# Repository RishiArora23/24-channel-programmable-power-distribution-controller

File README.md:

# 24-Channel Programmable Power Distribution Controller

An ESP32-based programmable firing controller for sequenced 24-channel power distribution. The system combines embedded firmware, a KiCad-designed PCB, and a PyQt5 desktop application to enable fully programmable, remotely triggered output sequences — with hardware safety interlocks and a real-time TFT display.

> ⚠️ **Safety Notice:** This system switches high-current loads via power MOSFETs. Always follow applicable electrical safety guidelines. Never connect live loads during programming or testing.

---

## How It Works

Each of the 24 output channels is driven by an **IRLZ44N N-Channel MOSFET** (55 V, 47 A) switched via a **3× cascaded shift register** chain. The ESP32 clocks channel states into the shift registers over SPI, allowing all 24 outputs to be independently toggled in any order or pattern. A 12 V rail MOSFET acts as a master power switch, controlled by software arm/disarm commands.

The desktop app (`main.py`) communicates with the ESP32 over **Wi-Fi (TCP port 8080)** or via **UDP auto-discovery** (port 4210). Sequences are authored graphically in the app, serialized to JSON, and uploaded to the ESP32 at runtime — no re-flashing required.

---

## System Architecture

```
[ PyQt5 Desktop App ] ──WiFi TCP/UDP──► [ ESP32 Firmware ]
         │                                      │
   Sequence Editor                    Shift Registers (×3)
   Group/Pattern UI                         │
   Arm / Fire Controls              [ 24× IRLZ44N MOSFETs ]
                                            │
                                    [ Output Terminals J1–J24 ]
```

---

## Hardware

**Key components (from KiCad schematic):**
- **MCU:** ESP32 (Arduino framework)
- **Output switches:** 24× IRLZ44N MOSFETs in TO-220 package
- **Channel indicators:** 24× LEDs with 220 Ω series resistors
- **Gate drive:** 10 kΩ pull-down resistors per MOSFET gate
- **Shift registers:** 3× 8-bit shift registers (SRCLK → pin 23, RCLK → pin 21, SER → pin 22, OE → pin 19, SRCLR → pin 18)
- **Rail safety:** MOSFET switch on pin 27, analog voltage sense on pin 34
- **Display:** ILI9341 TFT (HSPI: MOSI 13, CLK 14, MISO 12, CS 5, DC 4, RST 17)
- **Output connectors:** 24× 2-pin 5.08 mm terminal blocks (J1–J24)

**Project files:**

| File | Description |
|------|-------------|
| `*.kicad_sch` | Schematic (channel sub-sheets × 24 + top sheet) |
| `*.kicad_pcb` | PCB layout |
| `*.kicad_pro` | KiCad project file |

---

## Firmware (`*.ino`)

Written in Arduino C++ for ESP32. Key responsibilities:

- **WiFiManager** captive portal for first-time Wi-Fi setup (AP: `Pyro-Setup-AP`)
- TCP server on port **8080** for desktop app communication
- UDP listener on port **4210** for auto-discovery
- Shift register management: channels fire for **1000 ms** then auto-clear
- JSON sequence parser (`ArduinoJson`) supporting up to **20 groups × 24 steps**
- Built-in web UI accessible from any browser on the network (manual fire, arm/disarm, sequence status)
- Real-time TFT UI with state machine: `IDLE → ARMED → COUNTDOWN → EXECUTING → FINISHED`

**ESP32 Pin Summary:**

| Function | Pin |
|----------|-----|
| Rail MOSFET (arm) | 27 |
| Rail voltage sense | 34 |
| Shift reg SRCLK | 23 |
| Shift reg RCLK | 21 |
| Shift reg SER | 22 |
| Shift reg OE | 19 |
| Shift reg SRCLR | 18 |
| TFT MOSI/CLK/MISO/CS/DC/RST | 13/14/12/5/4/17 |

---

## Desktop App (`main.py`)

PyQt5 GUI application. Requires Python 3 and the following packages:

```bash
pip install PyQt5 pyserial
```

**Features:**
- Initialize a sequence with N cues (up to 24)
- Build named **groups** with patterns: Right Wave, Left Wave, Alternate, Center Burst, Inwards, All Fire
- Set inter-step gap (ms) per group
- Upload sequence as JSON to ESP32 over Wi-Fi
- Arm/disarm rail, monitor live rail voltage safety status
- Countdown display and per-channel LED flash feedback
- Undo/redo, save/load sequences as JSON files (`Ctrl+S` / `Ctrl+O`)
- **UDP Auto-Discovery** — finds the ESP32 on the local network automatically

**To run:**
```bash
python main.py
```

On first launch, connect the ESP32 to Wi-Fi via the `Pyro-Setup-AP` captive portal, then use **Auto Connect** in the app to discover it.

---

## Repository Structure

```
├── *.ino               # ESP32 Arduino firmware
├── main.py             # PyQt5 desktop control application
├── *.kicad_sch         # KiCad schematics (top + 24 channel sub-sheets)
├── *.kicad_pcb         # PCB layout
└── *.kicad_pro         # KiCad project
```

---

## License

This project is licensed under the [MIT License](LICENSE).

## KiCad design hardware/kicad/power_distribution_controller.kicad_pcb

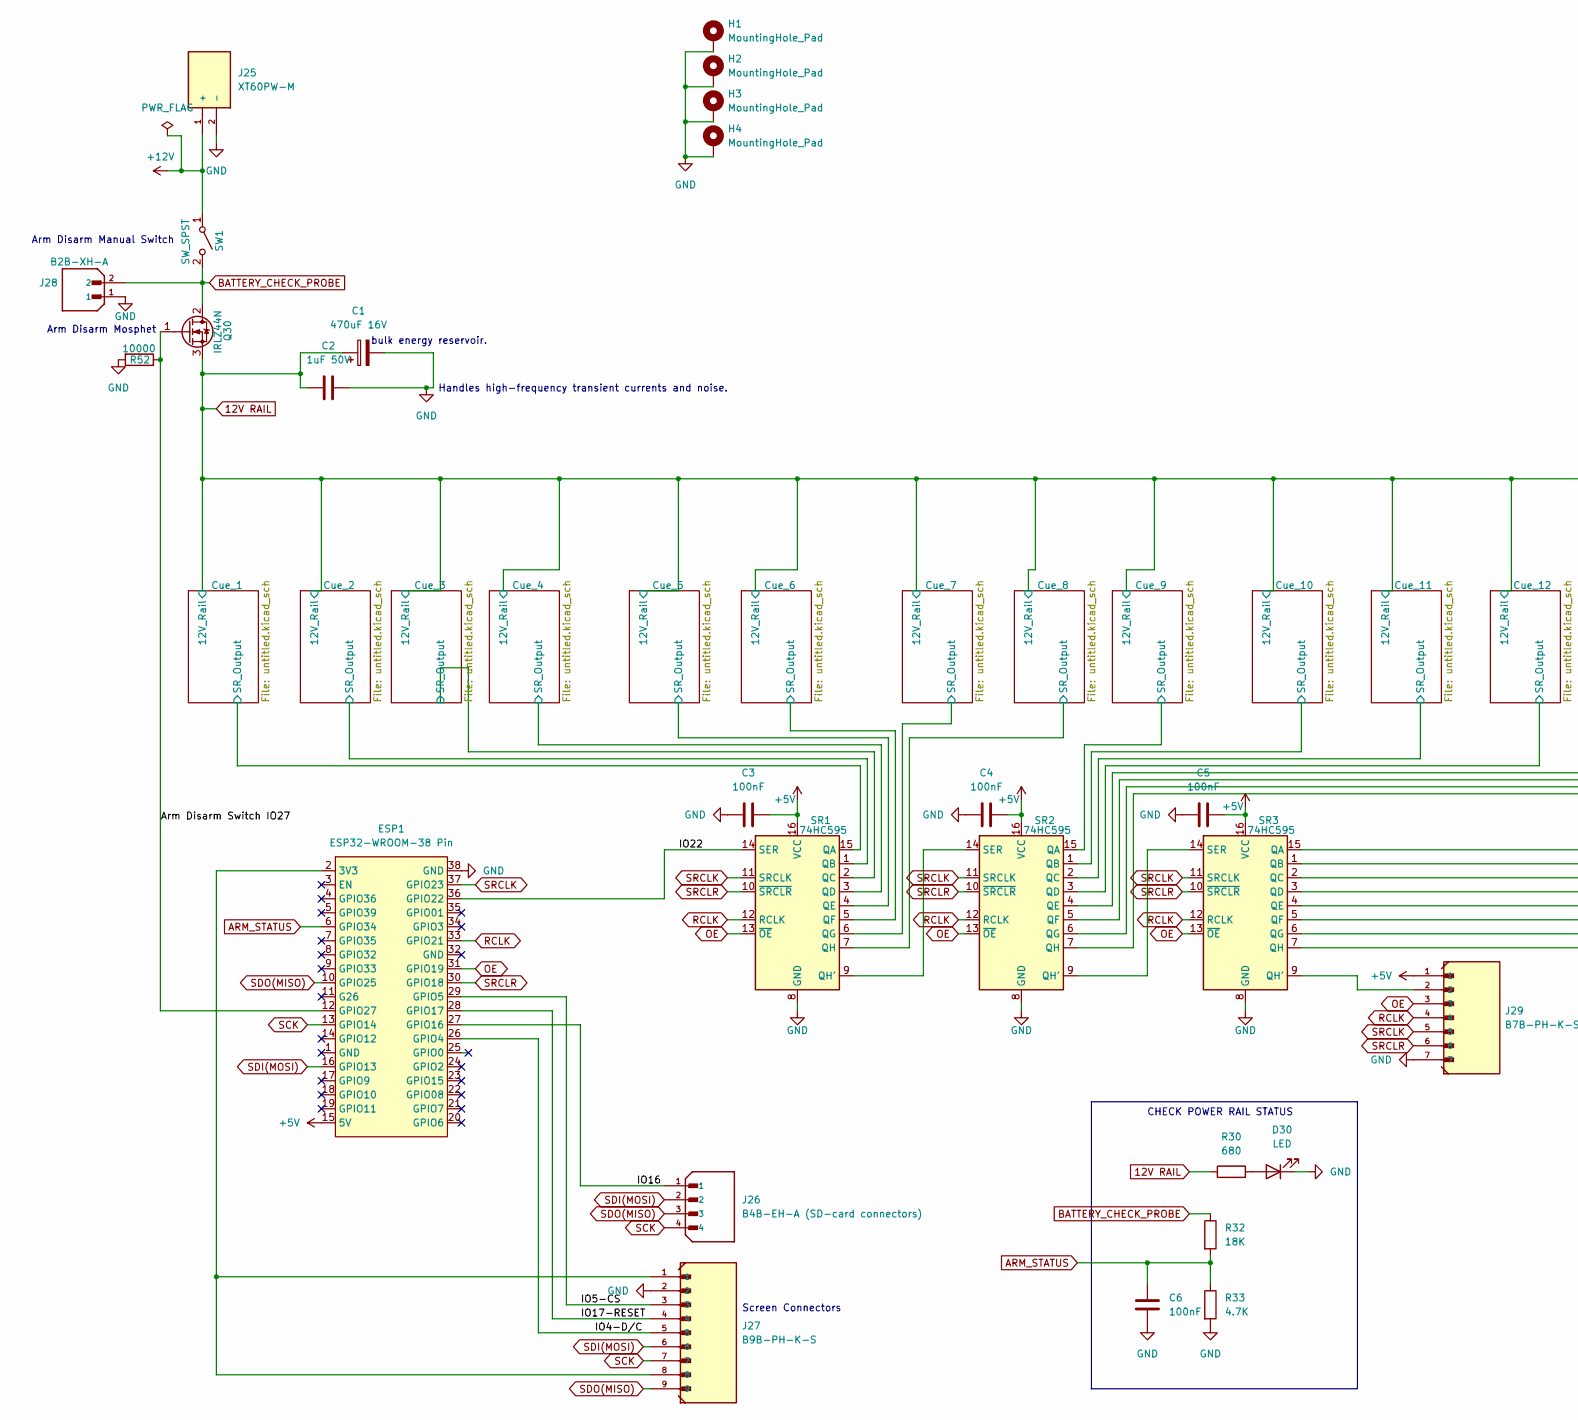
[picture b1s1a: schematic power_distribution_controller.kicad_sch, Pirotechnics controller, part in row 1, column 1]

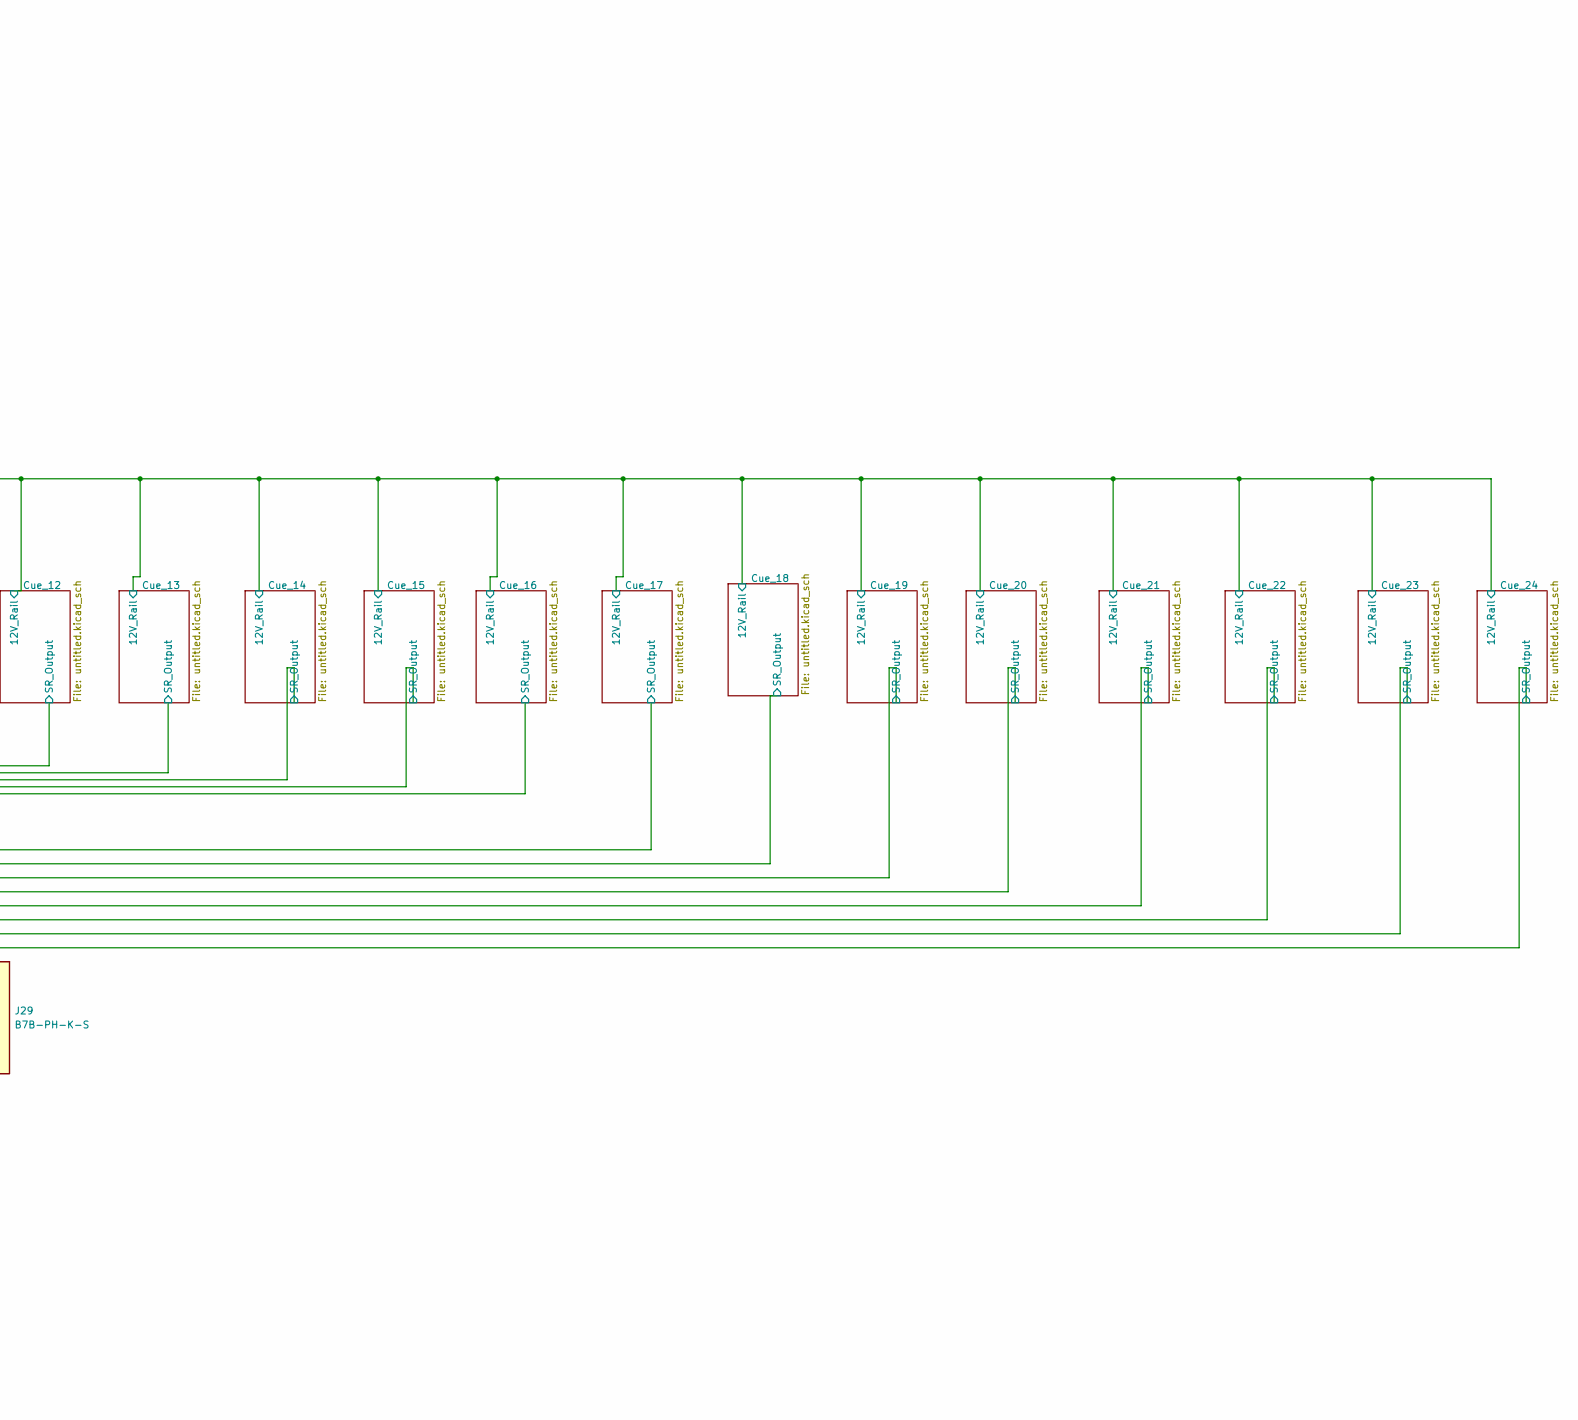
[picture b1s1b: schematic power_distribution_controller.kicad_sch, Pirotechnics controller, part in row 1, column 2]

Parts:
C1: 470uF 16V; CP_Radial_D10.0mm_P5.00mm
C2: 1uF 50V; CP_Radial_D5.0mm_P2.50mm
C3, C4, C5, C6: 100nF; C_0805_2012Metric_Pad1.18x1.45mm_HandSolder
D30: LED; LED_D5.0mm
ESP1: ESP32-WROOM-38 Pin; ESP32_38Pin_THT
H1, H2, H3, H4: MountingHole_Pad; MountingHole_3.2mm_M3_Pad
J25: XT60PW-M; AMASS_XT60PW-M; PARTREV V1.2
J26: B4B-EH-A (SD-card connectors); JST_PH_B4B-PH-K_1x04_P2.00mm_Vertical
J27: B9B-PH-K-S; JST_EH_B9B-EH-A_1x09_P2.50mm_Vertical
J28: B2B-XH-A; JST_B2B-XH-A; PARTREV N/A
J29: B7B-PH-K-S; JST_B7B-PH-K-S
Q30: IRLZ44N; TO-220-3_Vertical
R30: 680; R_0805_2012Metric_Pad1.20x1.40mm_HandSolder
R32: 18K; R_0805_2012Metric_Pad1.20x1.40mm_HandSolder
R33: 4.7K; R_0805_2012Metric_Pad1.20x1.40mm_HandSolder
R52: 10000; R_0805_2012Metric_Pad1.20x1.40mm_HandSolder
SR1, SR2, SR3: 74HC595; DIP-16_W7.62mm
SW1: SW_SPST; TerminalBlock_bornier-2_P5.08mm

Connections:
12V RAIL: C1.1, C2.1, Q30.3 (S), R30.1; also elsewhere on the board
+5V: C3.1, C4.1, C5.1, ESP1.15 (5V), J29.1, SR1.16 (VCC), SR2.16 (VCC), SR3.16 (VCC)
+12V: J25.1 (+), SW1.1 (A)
/Arm Disarm Switch IO27: ESP1.12 (GPIO27), Q30.1 (G), R52.1
/Cue_1/SR_Output: SR1.15 (QA); also elsewhere on the board
/Cue_2/SR_Output: SR1.1 (QB); also elsewhere on the board
/Cue_3/SR_Output: SR1.2 (QC); also elsewhere on the board
/Cue_4/SR_Output: SR1.3 (QD); also elsewhere on the board
/Cue_5/SR_Output: SR1.4 (QE); also elsewhere on the board
/Cue_6/SR_Output: SR1.5 (QF); also elsewhere on the board
/Cue_7/SR_Output: SR1.6 (QG); also elsewhere on the board
/Cue_8/SR_Output: SR1.7 (QH); also elsewhere on the board
/Cue_9/SR_Output: SR2.15 (QA); also elsewhere on the board
/Cue_10/SR_Output: SR2.1 (QB); also elsewhere on the board
/Cue_11/SR_Output: SR2.2 (QC); also elsewhere on the board
/Cue_12/SR_Output: SR2.3 (QD); also elsewhere on the board
/Cue_13/SR_Output: SR2.4 (QE); also elsewhere on the board
/Cue_14/SR_Output: SR2.5 (QF); also elsewhere on the board
/Cue_15/SR_Output: SR2.6 (QG); also elsewhere on the board
/Cue_16/SR_Output: SR2.7 (QH); also elsewhere on the board
/Cue_17/SR_Output: SR3.15 (QA); also elsewhere on the board
/Cue_18/SR_Output: SR3.1 (QB); also elsewhere on the board
/Cue_19/SR_Output: SR3.2 (QC); also elsewhere on the board
/Cue_20/SR_Output: SR3.3 (QD); also elsewhere on the board
/Cue_21/SR_Output: SR3.4 (QE); also elsewhere on the board
/Cue_22/SR_Output: SR3.5 (QF); also elsewhere on the board
/Cue_23/SR_Output: SR3.6 (QG); also elsewhere on the board
/Cue_24/SR_Output: SR3.7 (QH); also elsewhere on the board
/IO4-D/C: ESP1.26 (GPIO4), J27.5
/IO5-CS: ESP1.29 (GPIO5), J27.3
/IO16: ESP1.27 (GPIO16), J26.1
/IO17-RESET: ESP1.28 (GPIO17), J27.4
/IO22: ESP1.36 (GPIO22), SR1.14 (SER)
ARM_STATUS: C6.1, ESP1.6 (GPIO34), R32.2, R33.1
BATTERY_CHECK_PROBE: J28.2, Q30.2 (D), R32.1, SW1.2 (B)
GND: C1.2, C2.2, C3.2, C4.2, C5.2, C6.2, D30.1 (K), ESP1.38 (GND), H1.1, H2.1, H3.1, H4.1, J25.2 (-), J27.2, J28.1, J29.7, R33.2, R52.2, SR1.8 (GND), SR2.8 (GND), SR3.8 (GND); also elsewhere on the board
unnamed: D30.2 (A), R30.2
unnamed: ESP1.2 (3V3), J27.1, J27.8
unnamed: SR1.9 (QH'), SR2.14 (SER)
unnamed: SR2.9 (QH'), SR3.14 (SER)
unnamed: J29.2, SR3.9 (QH')
OE: ESP1.31 (GPIO19), J29.3, SR1.13 (~OE), SR2.13 (~OE), SR3.13 (~OE)
RCLK: ESP1.33 (GPIO21), J29.4, SR1.12 (RCLK), SR2.12 (RCLK), SR3.12 (RCLK)
SCK: ESP1.13 (GPIO14), J26.4, J27.7
SDI(MOSI): ESP1.16 (GPIO13), J26.2, J27.6
SDO(MISO): ESP1.10 (GPIO25), J26.3, J27.9
SRCLK: ESP1.37 (GPIO23), J29.5, SR1.11 (SRCLK), SR2.11 (SRCLK), SR3.11 (SRCLK)
SRCLR: ESP1.30 (GPIO18), J29.6, SR1.10 (~SRCLR), SR2.10 (~SRCLR), SR3.10 (~SRCLR)

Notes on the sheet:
Arm Disarm Mosphet
CHECK POWER RAIL STATUS
Screen Connectors
Arm Disarm Manual Switch
bulk energy reservoir.
Handles high-frequency transient currents and noise.

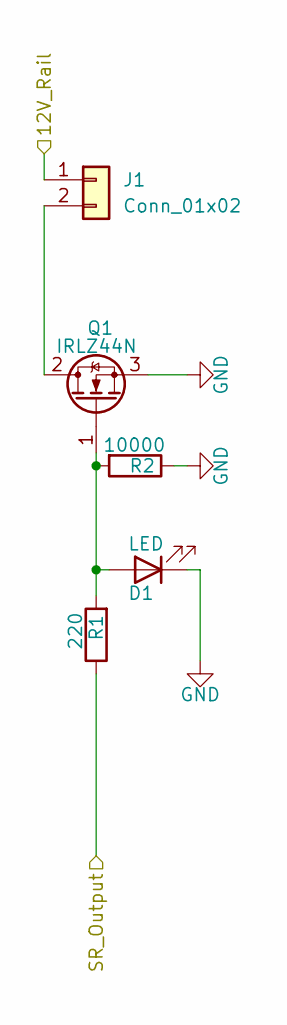
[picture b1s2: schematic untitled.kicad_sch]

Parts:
D1: LED; LED_D3.0mm
J1: Conn_01x02; TerminalBlock_bornier-2_P5.08mm
Q1: IRLZ44N; TO-220-3_Vertical
R1: 220; R_0805_2012Metric_Pad1.20x1.40mm_HandSolder
R2: 10000; R_0805_2012Metric_Pad1.20x1.40mm_HandSolder

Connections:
12V RAIL: J1.1; also elsewhere on the board
/Cue_1/SR_Output: R1.1; also elsewhere on the board
GND: D1.1 (K), Q1.3 (S), R2.1; also elsewhere on the board
unnamed: D1.2 (A), Q1.1 (G), R1.2, R2.2
unnamed: J1.2, Q1.2 (D)

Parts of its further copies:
D2, D3, D4, D5, D6, D7, D8, D9, D10, D11, D12, D13, D14, D15, D16, D17, D18, D19, D20, D21, D22, D23, D24: LED; LED_D3.0mm
J2, J3, J4, J5, J6, J7, J8, J9, J10, J11, J12, J13, J14, J15, J16, J17, J18, J19, J20, J21, J22, J23, J24: Conn_01x02; TerminalBlock_bornier-2_P5.08mm
Q2, Q3, Q4, Q5, Q6, Q7, Q8, Q9, Q10, Q11, Q12, Q13, Q14, Q15, Q16, Q17, Q18, Q19, Q20, Q21, Q22, Q23, Q24: IRLZ44N; TO-220-3_Vertical
R3, R5, R7, R9, R11, R13, R15, R17, R19, R21, R23, R25, R27, R29, R34, R36, R38, R40, R42, R44, R46, R48, R50: 220; R_0805_2012Metric_Pad1.20x1.40mm_HandSolder
R4, R6, R8, R10, R12, R14, R16, R18, R20, R22, R24, R26, R28, R31, R35, R37, R39, R41, R43, R45, R47, R49, R51: 10000; R_0805_2012Metric_Pad1.20x1.40mm_HandSolder

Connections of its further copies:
12V RAIL: J2.1, J3.1, J4.1, J5.1, J6.1, J7.1, J8.1, J9.1, J10.1, J11.1, J12.1, J13.1, J14.1, J15.1, J16.1, J17.1, J18.1, J19.1, J20.1, J21.1, J22.1, J23.1, J24.1; also elsewhere on the board
/Cue_2/SR_Output: R3.1; also elsewhere on the board
/Cue_3/SR_Output: R5.1; also elsewhere on the board
/Cue_4/SR_Output: R7.1; also elsewhere on the board
/Cue_5/SR_Output: R9.1; also elsewhere on the board
/Cue_6/SR_Output: R11.1; also elsewhere on the board
/Cue_7/SR_Output: R13.1; also elsewhere on the board
/Cue_8/SR_Output: R15.1; also elsewhere on the board
/Cue_9/SR_Output: R17.1; also elsewhere on the board
/Cue_10/SR_Output: R19.1; also elsewhere on the board
/Cue_11/SR_Output: R21.1; also elsewhere on the board
/Cue_12/SR_Output: R23.1; also elsewhere on the board
/Cue_13/SR_Output: R25.1; also elsewhere on the board
/Cue_14/SR_Output: R27.1; also elsewhere on the board
/Cue_15/SR_Output: R29.1; also elsewhere on the board
/Cue_16/SR_Output: R34.1; also elsewhere on the board
/Cue_17/SR_Output: R36.1; also elsewhere on the board
/Cue_18/SR_Output: R38.1; also elsewhere on the board
/Cue_19/SR_Output: R40.1; also elsewhere on the board
/Cue_20/SR_Output: R42.1; also elsewhere on the board
/Cue_21/SR_Output: R44.1; also elsewhere on the board
/Cue_22/SR_Output: R46.1; also elsewhere on the board
/Cue_23/SR_Output: R48.1; also elsewhere on the board
/Cue_24/SR_Output: R50.1; also elsewhere on the board
GND: D2.1 (K), D3.1 (K), D4.1 (K), D5.1 (K), D6.1 (K), D7.1 (K), D8.1 (K), D9.1 (K), D10.1 (K), D11.1 (K), D12.1 (K), D13.1 (K), D14.1 (K), D15.1 (K), D16.1 (K), D17.1 (K), D18.1 (K), D19.1 (K), D20.1 (K), D21.1 (K), D22.1 (K), D23.1 (K), D24.1 (K), Q2.3 (S), Q3.3 (S), Q4.3 (S), Q5.3 (S), Q6.3 (S), Q7.3 (S), Q8.3 (S), Q9.3 (S), Q10.3 (S), Q11.3 (S), Q12.3 (S), Q13.3 (S), Q14.3 (S), Q15.3 (S), Q16.3 (S), Q17.3 (S), Q18.3 (S), Q19.3 (S), Q20.3 (S), Q21.3 (S), Q22.3 (S), Q23.3 (S), Q24.3 (S), R4.1, R6.1, R8.1, R10.1, R12.1, R14.1, R16.1, R18.1, R20.1, R22.1, R24.1, R26.1, R28.1, R31.1, R35.1, R37.1, R39.1, R41.1, R43.1, R45.1, R47.1, R49.1, R51.1; also elsewhere on the board
unnamed: D2.2 (A), Q2.1 (G), R3.2, R4.2
unnamed: D3.2 (A), Q3.1 (G), R5.2, R6.2
unnamed: D4.2 (A), Q4.1 (G), R7.2, R8.2
unnamed: D5.2 (A), Q5.1 (G), R9.2, R10.2
unnamed: D6.2 (A), Q6.1 (G), R11.2, R12.2
unnamed: D7.2 (A), Q7.1 (G), R13.2, R14.2
unnamed: D8.2 (A), Q8.1 (G), R15.2, R16.2
unnamed: D9.2 (A), Q9.1 (G), R17.2, R18.2
unnamed: D10.2 (A), Q10.1 (G), R19.2, R20.2
unnamed: D11.2 (A), Q11.1 (G), R21.2, R22.2
unnamed: D12.2 (A), Q12.1 (G), R23.2, R24.2
unnamed: D13.2 (A), Q13.1 (G), R25.2, R26.2
unnamed: D14.2 (A), Q14.1 (G), R27.2, R28.2
unnamed: D15.2 (A), Q15.1 (G), R29.2, R31.2
unnamed: D16.2 (A), Q16.1 (G), R34.2, R35.2
unnamed: D17.2 (A), Q17.1 (G), R36.2, R37.2
unnamed: D18.2 (A), Q18.1 (G), R38.2, R39.2
unnamed: D19.2 (A), Q19.1 (G), R40.2, R41.2
unnamed: D20.2 (A), Q20.1 (G), R42.2, R43.2
unnamed: D21.2 (A), Q21.1 (G), R44.2, R45.2
unnamed: D22.2 (A), Q22.1 (G), R46.2, R47.2
unnamed: D23.2 (A), Q23.1 (G), R48.2, R49.2
unnamed: D24.2 (A), Q24.1 (G), R50.2, R51.2
unnamed: J2.2, Q2.2 (D)
unnamed: J3.2, Q3.2 (D)
unnamed: J4.2, Q4.2 (D)
unnamed: J5.2, Q5.2 (D)
unnamed: J6.2, Q6.2 (D)
unnamed: J7.2, Q7.2 (D)
unnamed: J8.2, Q8.2 (D)
unnamed: J9.2, Q9.2 (D)
unnamed: J10.2, Q10.2 (D)
unnamed: J11.2, Q11.2 (D)
unnamed: J12.2, Q12.2 (D)
unnamed: J13.2, Q13.2 (D)
unnamed: J14.2, Q14.2 (D)
unnamed: J15.2, Q15.2 (D)
unnamed: J16.2, Q16.2 (D)
unnamed: J17.2, Q17.2 (D)
unnamed: J18.2, Q18.2 (D)
unnamed: J19.2, Q19.2 (D)
unnamed: J20.2, Q20.2 (D)
unnamed: J21.2, Q21.2 (D)
unnamed: J22.2, Q22.2 (D)
unnamed: J23.2, Q23.2 (D)
unnamed: J24.2, Q24.2 (D)

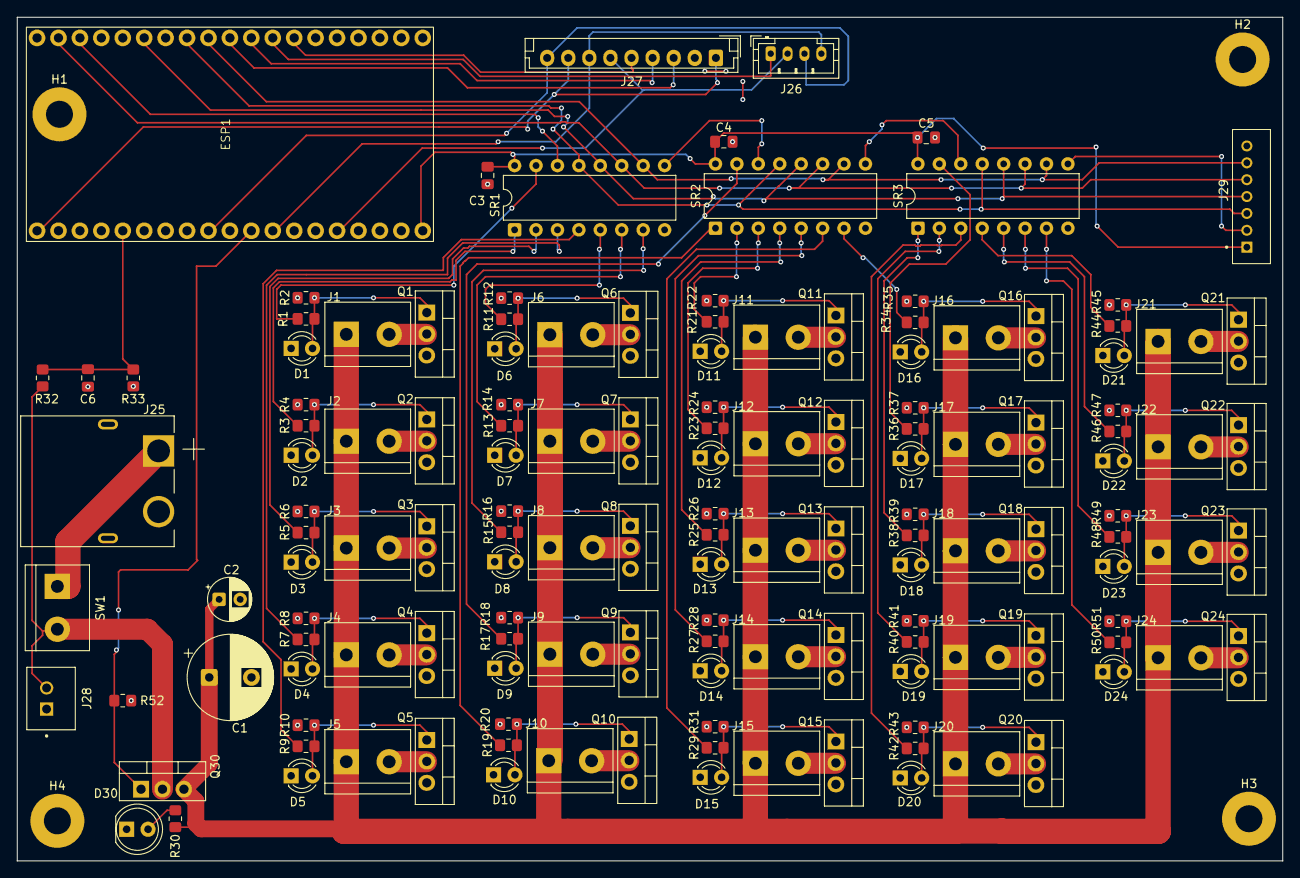
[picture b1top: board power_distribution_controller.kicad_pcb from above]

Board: 2 copper layers, 150.0 x 100.0 mm, 146 parts (0 on the bottom side), 96 nets.

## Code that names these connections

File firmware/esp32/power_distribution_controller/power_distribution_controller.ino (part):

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Adafruit_ILI9341 tft = Adafruit_ILI9341(&hspi, TFT_DC, TFT_CS, TFT_RST);

// --- Shift Register Pins ---
#define SRCLK_PIN 23
#define RCLK_PIN 21
#define SER_PIN 22
#define OE_PIN 19
#define SRCLR_PIN 18

// --- System Limits ---
#define NUM_SHIFT_REGISTERS 3
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// SECTION 8: Hardware & UDP Init
// ==========================================================================
void setupHardware() {
    pinMode(SRCLK_PIN, OUTPUT);
    pinMode(RCLK_PIN, OUTPUT);
    pinMode(SER_PIN, OUTPUT);
    pinMode(OE_PIN, OUTPUT);
    pinMode(SRCLR_PIN, OUTPUT);
    
    pinMode(PIN_RAIL_MOSFET, OUTPUT);
    digitalWrite(PIN_RAIL_MOSFET, LOW); 
    pinMode(PIN_RAIL_SENSE, INPUT); 

    digitalWrite(SRCLR_PIN, HIGH);
    digitalWrite(OE_PIN, LOW);
    digitalWrite(RCLK_PIN, LOW);
    digitalWrite(SRCLK_PIN, LOW);
    digitalWrite(SER_PIN, LOW);

    clearAllOutputs();
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void clearAllOutputs() {
    byte cleanState[NUM_SHIFT_REGISTERS] = {0}; 
    digitalWrite(OE_PIN, HIGH);
    digitalWrite(RCLK_PIN, LOW);
    shiftOut(SER_PIN, SRCLK_PIN, MSBFIRST, cleanState[2]);
    shiftOut(SER_PIN, SRCLK_PIN, MSBFIRST, cleanState[1]);
    shiftOut(SER_PIN, SRCLK_PIN, MSBFIRST, cleanState[0]);
    digitalWrite(RCLK_PIN, HIGH);
    digitalWrite(OE_PIN, LOW);

    memset(shiftRegisterStates, 0, sizeof(shiftRegisterStates));
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
void updateShiftRegisters() {
    digitalWrite(OE_PIN, HIGH);
    digitalWrite(RCLK_PIN, LOW);
    shiftOut(SER_PIN, SRCLK_PIN, MSBFIRST, shiftRegisterStates[2]);
    shiftOut(SER_PIN, SRCLK_PIN, MSBFIRST, shiftRegisterStates[1]);
    shiftOut(SER_PIN, SRCLK_PIN, MSBFIRST, shiftRegisterStates[0]);
    digitalWrite(RCLK_PIN, HIGH);
    digitalWrite(OE_PIN, LOW);
}

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
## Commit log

2026-05-26 Revise README for comprehensive project documentation
    Expanded README with detailed project overview, safety notice, system architecture, hardware components, firmware responsibilities, desktop app features, and repository structure.
2026-05-26 Revise LICENSE with new copyright and restrictions
    Updated the license details and added restrictions on usage.
2026-05-26 Add new files
